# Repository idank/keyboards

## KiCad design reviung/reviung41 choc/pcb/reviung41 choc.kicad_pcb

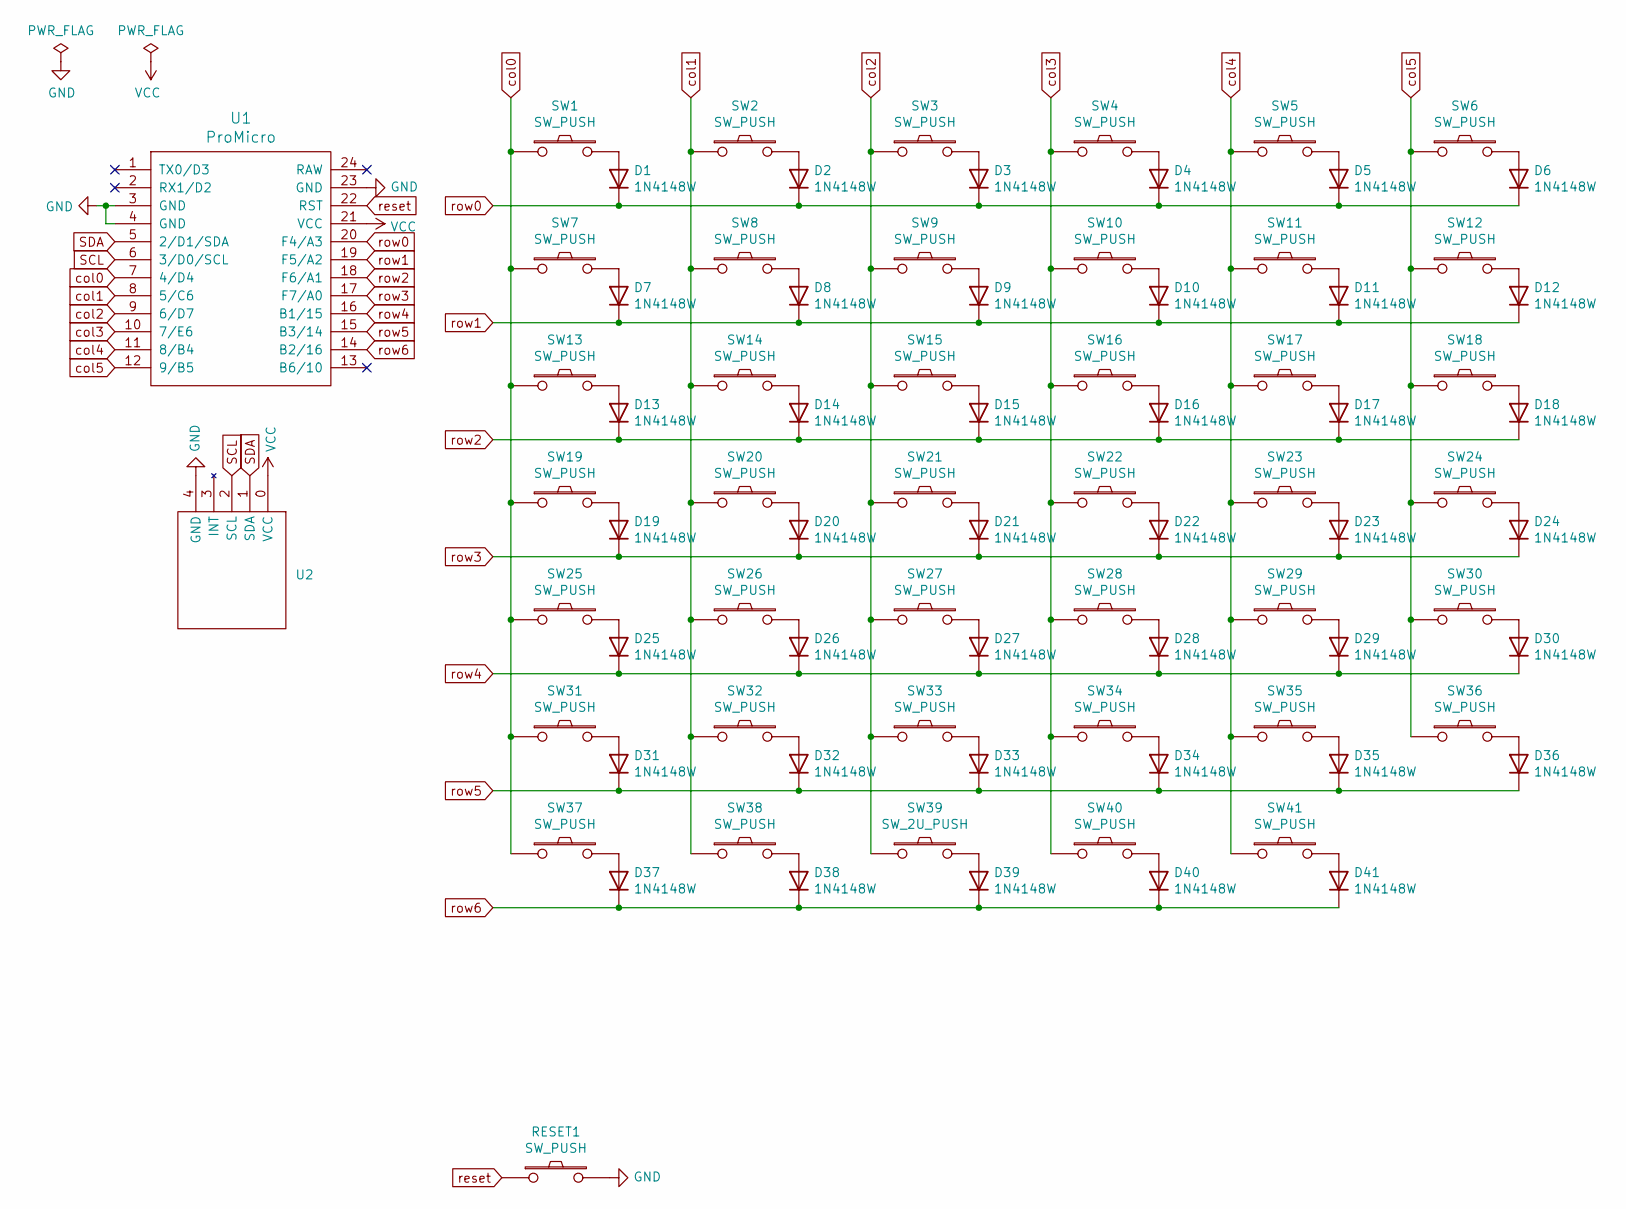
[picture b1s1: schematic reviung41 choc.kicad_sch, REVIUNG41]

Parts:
D1, D2, D3, D4, D5, D6, D7, D8, D9, D10, D11, D12, D13, D14, D15, D16, D17, D18, D19, D20, D21, D22, D23, D24, D25, D26, D27, D28, D29, D30, D31, D32, D33, D34, D35, D36, D37, D38, D39, D40, D41: 1N4148W; D3_SMD_v2
RESET1: SW_PUSH; ResetSW_1side
SW1, SW2, SW3, SW4, SW5, SW6, SW7, SW8, SW9, SW10, SW11, SW12, SW13, SW14, SW15, SW16, SW17, SW18, SW19, SW20, SW21, SW22, SW23, SW24, SW25, SW26, SW27, SW28, SW29, SW30, SW31, SW32, SW33, SW34, SW35, SW36, SW37, SW38, SW40, SW41: SW_PUSH; Kailh_socket_PG1350_optional_oval_1
SW39: SW_2U_PUSH; Kailh_socket_PG1350_optional_oval_1
U1: ProMicro; ProMicro_v3
U2: pim447

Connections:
GND: RESET1.2, U1.3 (GND), U1.4 (GND), U1.23 (GND), U2.4 (GND)
unnamed: D1.2 (A), SW1.2
unnamed: D2.2 (A), SW2.2
unnamed: D3.2 (A), SW3.2
unnamed: D4.2 (A), SW4.2
unnamed: D5.2 (A), SW5.2
unnamed: D6.2 (A), SW6.2
unnamed: D7.2 (A), SW7.2
unnamed: D8.2 (A), SW8.2
unnamed: D9.2 (A), SW9.2
unnamed: D10.2 (A), SW10.2
unnamed: D11.2 (A), SW11.2
unnamed: D12.2 (A), SW12.2
unnamed: D13.2 (A), SW13.2
unnamed: D14.2 (A), SW14.2
unnamed: D15.2 (A), SW15.2
unnamed: D16.2 (A), SW16.2
unnamed: D17.2 (A), SW17.2
unnamed: D18.2 (A), SW18.2
unnamed: D19.2 (A), SW19.2
unnamed: D20.2 (A), SW20.2
unnamed: D21.2 (A), SW21.2
unnamed: D22.2 (A), SW22.2
unnamed: D23.2 (A), SW23.2
unnamed: D24.2 (A), SW24.2
unnamed: D25.2 (A), SW25.2
unnamed: D26.2 (A), SW26.2
unnamed: D27.2 (A), SW27.2
unnamed: D28.2 (A), SW28.2
unnamed: D29.2 (A), SW29.2
unnamed: D30.2 (A), SW30.2
unnamed: D31.2 (A), SW31.2
unnamed: D32.2 (A), SW32.2
unnamed: D33.2 (A), SW33.2
unnamed: D34.2 (A), SW34.2
unnamed: D35.2 (A), SW35.2
unnamed: D36.2 (A), SW36.2
unnamed: D37.2 (A), SW37.2
unnamed: D38.2 (A), SW38.2
unnamed: D39.2 (A), SW39.2
unnamed: D40.2 (A), SW40.2
unnamed: D41.2 (A), SW41.2
SCL: U1.6 (3/D0/SCL), U2.2 (SCL)
SDA: U1.5 (2/D1/SDA), U2.1 (SDA)
VCC: U1.21 (VCC), U2.0 (VCC)
col0: SW1.1, SW7.1, SW13.1, SW19.1, SW25.1, SW31.1, SW37.1, U1.7 (4/D4)
col1: SW2.1, SW8.1, SW14.1, SW20.1, SW26.1, SW32.1, SW38.1, U1.8 (5/C6)
col2: SW3.1, SW9.1, SW15.1, SW21.1, SW27.1, SW33.1, SW39.1, U1.9 (6/D7)
col3: SW4.1, SW10.1, SW16.1, SW22.1, SW28.1, SW34.1, SW40.1, U1.10 (7/E6)
col4: SW5.1, SW11.1, SW17.1, SW23.1, SW29.1, SW35.1, SW41.1, U1.11 (8/B4)
col5: SW6.1, SW12.1, SW18.1, SW24.1, SW30.1, SW36.1, U1.12 (9/B5)
reset: RESET1.1, U1.22 (RST)
row0: D1.1 (K), D2.1 (K), D3.1 (K), D4.1 (K), D5.1 (K), D6.1 (K), U1.20 (F4/A3)
row1: D7.1 (K), D8.1 (K), D9.1 (K), D10.1 (K), D11.1 (K), D12.1 (K), U1.19 (F5/A2)
row2: D13.1 (K), D14.1 (K), D15.1 (K), D16.1 (K), D17.1 (K), D18.1 (K), U1.18 (F6/A1)
row3: D19.1 (K), D20.1 (K), D21.1 (K), D22.1 (K), D23.1 (K), D24.1 (K), U1.17 (F7/A0)
row4: D25.1 (K), D26.1 (K), D27.1 (K), D28.1 (K), D29.1 (K), D30.1 (K), U1.16 (B1/15)
row5: D31.1 (K), D32.1 (K), D33.1 (K), D34.1 (K), D35.1 (K), D36.1 (K), U1.15 (B3/14)
row6: D37.1 (K), D38.1 (K), D39.1 (K), D40.1 (K), D41.1 (K), U1.14 (B2/16)

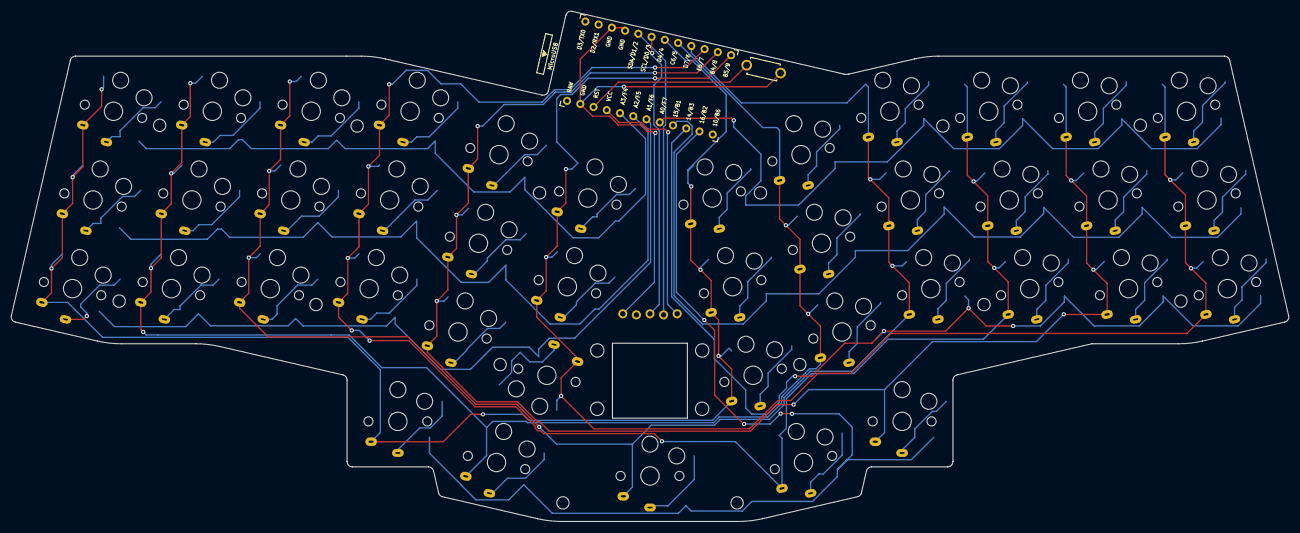
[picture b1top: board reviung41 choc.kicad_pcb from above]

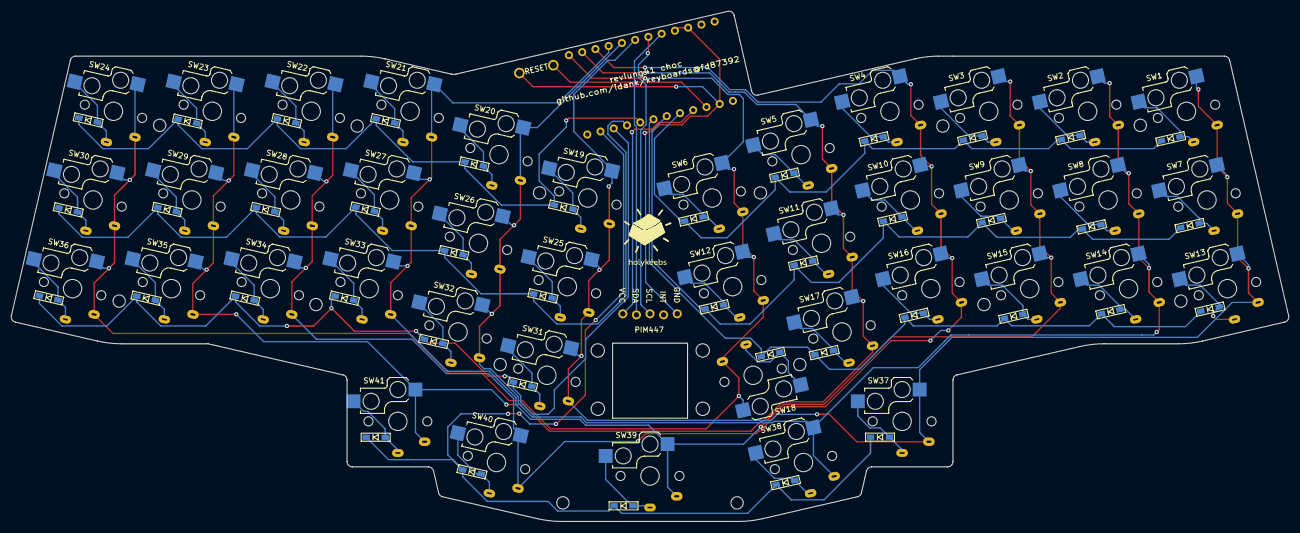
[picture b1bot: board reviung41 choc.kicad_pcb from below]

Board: 2 copper layers, 238.7 x 95.3 mm, 86 parts (41 on the bottom side), 59 nets.

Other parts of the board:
rev41lp_edgecutPCB: rev41lp_edgecutPCB

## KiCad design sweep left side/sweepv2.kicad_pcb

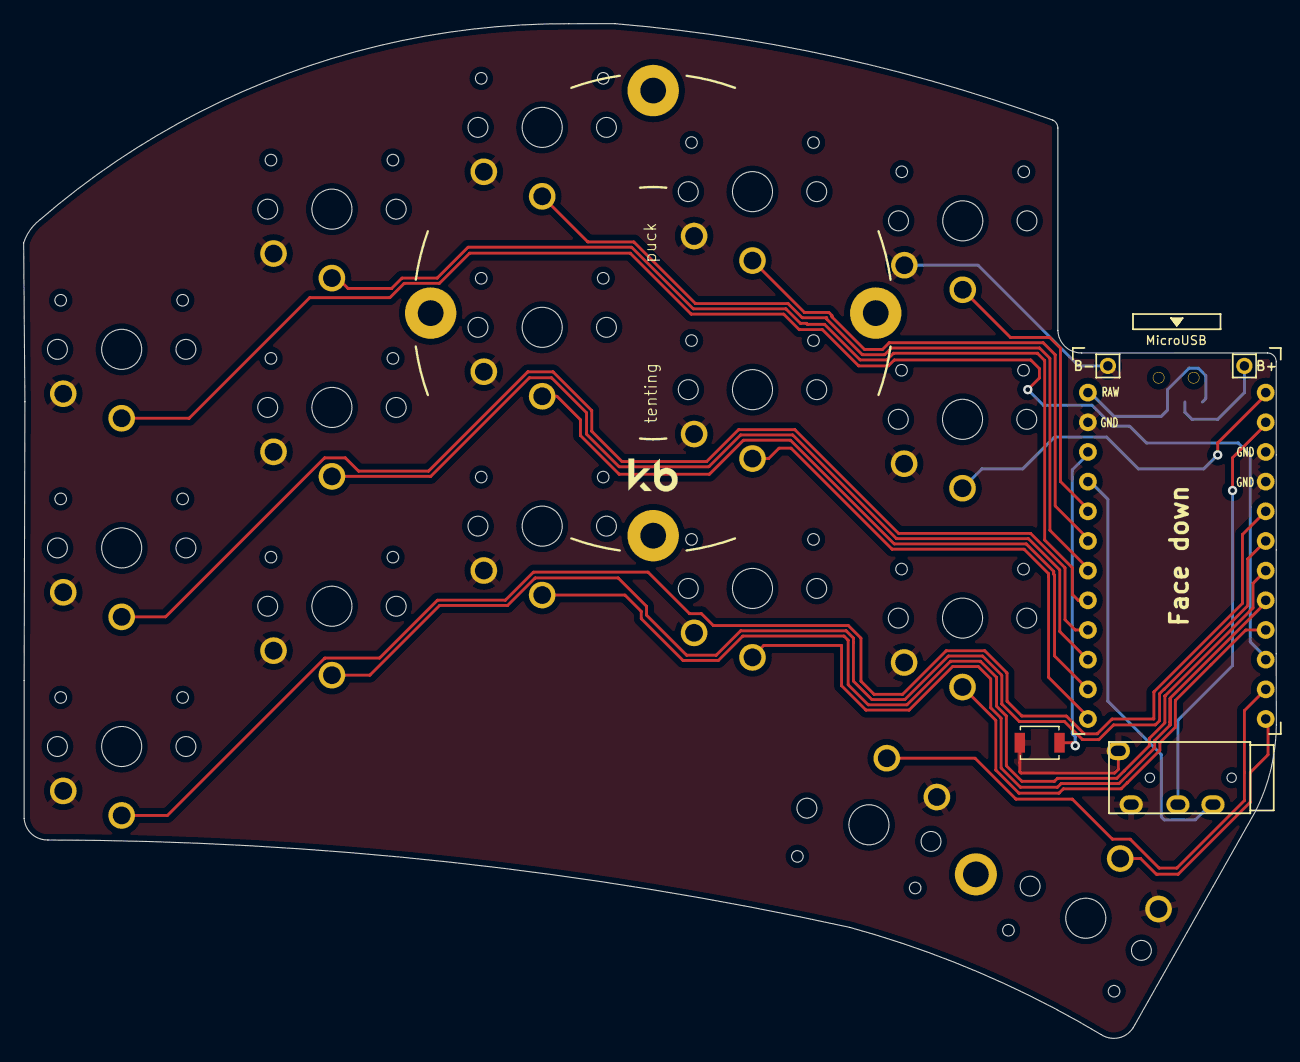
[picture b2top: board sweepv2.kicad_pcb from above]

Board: 2 copper layers, 107.2 x 86.9 mm, 23 parts (1 on the bottom side), 23 nets.

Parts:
B+: MountingHole_Pad; 1pin_conn
B-: MountingHole_Pad; 1pin_conn
J2: AudioJack4dpb; TRRS-PJ-320A
POWER SW: SW_SPDT; SPDT_C128955
RSW1: SW_Push; SW_SPST_B3U-1000P
SW2, SW3, SW4, SW5, SW6, SW8, SW9, SW10, SW11, SW12, SW14, SW15, SW16, SW17, SW18, SW20, SW21: SW_Push; choc-v1-with-millmax
U1: ProMicro-kbd; ProMicro_v3_min

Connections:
BT+_r: B+.1, POWER SW.2
Switch1: SW2.1, U1.10
Switch2: SW3.1, U1.17
Switch3: SW4.1, U1.18
Switch4: SW5.1, U1.19
Switch5: SW6.1, U1.20
Switch6: SW8.1, U1.16
Switch7: SW9.1, U1.15
Switch8: SW10.1, U1.14
Switch9: SW11.1, U1.13
Switch10: SW12.1, U1.1
Switch11: SW14.1, U1.5
Switch12: SW15.1, U1.6
Switch13: SW16.1, U1.7
Switch14: SW17.1, U1.8
Switch15: SW18.1, U1.9
Switch16: SW21.1, U1.11
Switch17: SW20.1, U1.12
Switch18: J2.R1, U1.2
gnd: B-.1, J2.S, J2.T, RSW1.1, SW2.2, SW3.2, SW4.2, SW5.2, SW6.2, SW8.2, SW9.2, SW10.2, SW11.2, SW12.2, SW14.2, SW15.2, SW16.2, SW17.2, SW18.2, SW20.2, SW21.2, U1.3, U1.4, U1.23
raw: POWER SW.3, U1.24
reset: RSW1.2, U1.22
vcc: J2.R2, U1.21
